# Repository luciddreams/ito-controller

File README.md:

# ITO Controller — Condensation Mirror

KiCad 9 project for a 100 × 100 mm ITO glass plate with resistive heating and four independently regulated TEC1-12706 cooling channels. Controller: Seeed XIAO BLE nRF52840. Supply: Mean Well GST160A24-R7B, connected directly to J30 (Kycon KPJX-4S).

**Status:** revision L, supervised prototype; no assembled hardware has been tested. Maximum actual total input current: 4 A. Firmware L.1 supports short manual tests with one TEC at a time. Automatic condensation/dew-point control is not implemented.

## Start here

- [Detailed project description](docs/PROJECT-DESCRIPTION.md): circuit operation, thermal concept, operating limits and outstanding work.
- [Schematic PDF](ito-controller-schema-rev-l.pdf) and [schematic reading guide](SCHEMATIC-GUIDE.md).
- Open `ito-controller.kicad_pro` in KiCad 9 for the schematic, PCB and 3D viewer. Keep the directory structure intact.
- [Datasheets and BOM coverage](datasheets/README.md).
- [Purchasing BOM and order tracker](procurement/README.md): ordered/delivered checkboxes, suppliers, prices and quantities.
- [Assembly and wiring](ASSEMBLY.md), [connector pinout](connector-pinout.csv) and [prototype commissioning](PROTOTYPE-START.md).
- [Firmware build, flashing and calibration](firmware/README.md) and [GPIO/I²C contract](FIRMWARE-INTERFACE.md).

## Repository contents

| Path | Contents |
|---|---|
| `ito-controller.kicad_*`, `sheet_*.kicad_sch` | Editable PCB and 14-page schematic |
| `ITO.kicad_sym`, `ITO_PCB.pretty/`, `3dmodels/` | Local symbols, footprints and models |
| `manufacturing/` | Gerbers, drills, placement files and fabrication output |
| `BOM-prototype.csv` | Component references, manufacturers and orderable part numbers |
| `external-sensor-BOM.csv` | External ambient modules and cable parts |
| `procurement/` | Browser purchasing tracker, Excel alternative and instructions |
| `firmware/` | Source code, diagnostic build and host tests |
| `datasheets/` | Manufacturer documents, source URLs and download status |
| `docs/` | Detailed description and import information |
| `*-review.json`, `*-parity.json`, `*.rpt` | Design checks and comparison reports |
| `commissioning-results.csv` | Physical tests awaiting execution |
| `history-rev-j/`, `history-rev-k/` | Historical records; not current construction instructions |

## Fabrication and verification

Read [FABRICATION.md](FABRICATION.md) before ordering: four layers, 160 × 110 mm, 1.6 mm thick, 70/35/35/70 µm copper, with specified via-in-pad processing. Assemble one prototype first.

Existing reports record zero ERC/DRC violations and schematic/PCB parity for 202 components and 638 pins. The readable-schematic revision preserved the PCB. Design checks and firmware host tests do not replace physical commissioning.

## Next engineering steps

1. Select the exact NTC probes, fan, cooling assembly and glass coating.
2. Inspect the unloaded board and verify auxiliary supplies.
3. Measure with dummy loads and enter firmware calibration data.
4. Qualify one TEC, then the glass, using short limited-power pulses.
5. Develop four-channel operation and automatic dew-point control only after qualification.

Remote SHT31 sensors require the complete adapter and jumper instructions in [REMOTE-SENSORS.md](REMOTE-SENSORS.md). Their RJ45 links are not Ethernet or PoE.

## Language and licensing

English is the working language for current documentation and schematic annotations. Original historical engineering records are retained in their original language for traceability; see [historical records](docs/HISTORICAL-RECORDS.md). Manufacturer PDFs retain the language supplied by their authors. Legacy component Value fields and net identifiers remain stable for CAD/BOM compatibility.

No open-source license has been selected for the project's own hardware or firmware. Third-party documents and models retain their original rights and licenses; see [THIRD-PARTY-NOTICES.md](THIRD-PARTY-NOTICES.md).

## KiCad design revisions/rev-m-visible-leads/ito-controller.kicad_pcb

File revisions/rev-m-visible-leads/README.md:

# Revision M — visible-lead prototype

This independent KiCad project replaces the five QFN ICs in revision L. Signal pins on U1 and U11–U14 are exposed gull-wing leads. Their grounded thermal pads still require soldering. The original manufactured design at the repository root is unchanged.

**Engineering prototype, not a bench-qualified production release.** See `review/STATUS.md` for the actual checks and outstanding release gates. Do not use revision-L Gerbers, stencil, component placement or calibration for this board.

## Main changes

| Circuit | Revision L | Revision M |
|---|---|---|
| U1 input eFuse | TPS26630RGER, QFN24 | TPS26631PWPR, HTSSOP20 + ground pad |
| U11–U14 TEC control | LT8613EUDE, QFN28 | LT3741EFE-1#PBF, TSSOP20 + ground pad |
| TEC switches | Inside LT8613 | Two IRLR024NTRPBF DPAK MOSFETs per channel |
| L1–L4 | 10 µH IHLP6767 | 33 µH Bourns SRP1265A-330M |
| Switching frequency | Nominal 500 kHz | Nominal 300 kHz |
| TP11–TP14 monitoring | LT8613 IMON | INA180A1IDBVR, SOT23-5, 0.5 V/A nominal |
| Board | 160 × 110 mm, four layers | 160 × 128 mm, four layers |

The upper mounting holes and four TEC connector locations are retained. Lower circuitry, lower mounting holes and the antenna keepout move down 18 mm. This revision therefore requires a mechanical fit check. The lower schematic functions, GPIO assignments, I²C addresses, relay/thermostat chain and heater interlock remain unchanged.

Open **`ito-controller.kicad_pro` in this directory** with KiCad 9. The symbol and footprint libraries are local. Existing 3D models are referenced from `../../3dmodels`; new package footprints currently have no 3D models. Electrical and fabrication geometry does not depend on those models.

## Electrical differences that matter

- TPS26631 is **not fault-identical** to TPS26630. After PGOOD, it permits approximately twice the programmed current for nominally 25.5 ms. With 4.02 kΩ, nominal sustained limit is approximately 4.48 A and the temporary limit approximately 8.96 A. Actual operating input current must still remain at or below 4 A. Verify the adapter, fuse, reset and interlock response with the new eFuse.
- LT3741-1 controls **average inductor current** and does not intentionally sink current. The 25 mΩ shunt is now before the output capacitors. TP monitoring therefore includes inductor ripple and capacitor charging current. Use an external meter/current probe in the TEC lead for load-current calibration.
- R42/R44/R46/R48 change to 4.02 kΩ. The lower 10 kΩ resistors and buffers remain. Full DAC code gives approximately 1.460 V at CTRL1. Expected nominal full-scale current is about 1.99 A using the 51 mV reference specification; part tolerances can produce over 2 A. This is **not a guaranteed 2 A limiter**. Calibrate each channel and use conservative code limits.
- The nominal voltage ceiling is 11.94 V. The 22.1 kΩ / 6.8 nF compensation network is a calculated starting point. C109/C209/C309/C409 are optional 100 pF compensation footprints and **DNP** initially.
- IRLR024N has a maximum 2 V threshold at 25 °C, at the boundary of ADI's recommendation of less than 2 V. Startup/recovery and cold operation are explicit qualification gates. The footprint permits reviewing another pin-compatible DPAK part if this gate fails; substitution is not automatic.

The diagnostic firmware at `../../firmware` writes raw DAC codes and retains the same GPIO/I²C interface. Use its default disabled calibration state. **Do not carry over measured TEC code limits from revision L.** This revision does not turn that firmware into an automatic or unattended controller.

## Files

- Native schematics, PCB and local libraries: editable design.
- `design.json`: component pin/net and ordering data.
- `BOM-prototype.csv`: individual references; Fit column identifies the four DNP options.
- `review/`: calculation results, clean ERC/DRC/parity reports and prototype test gates.
- `fabrication/`: prototype Gerber/drill archive and manufacturing notes.
- `tools/`: reproducible design transformation, calculation and audit helpers. Generation starts from the unchanged revision-L project; final routed PCB is the authoritative layout.

Changing a package or component value can affect compensation, protection or assembly. Read `review/DESIGN-REVIEW.md` before ordering alternatives.

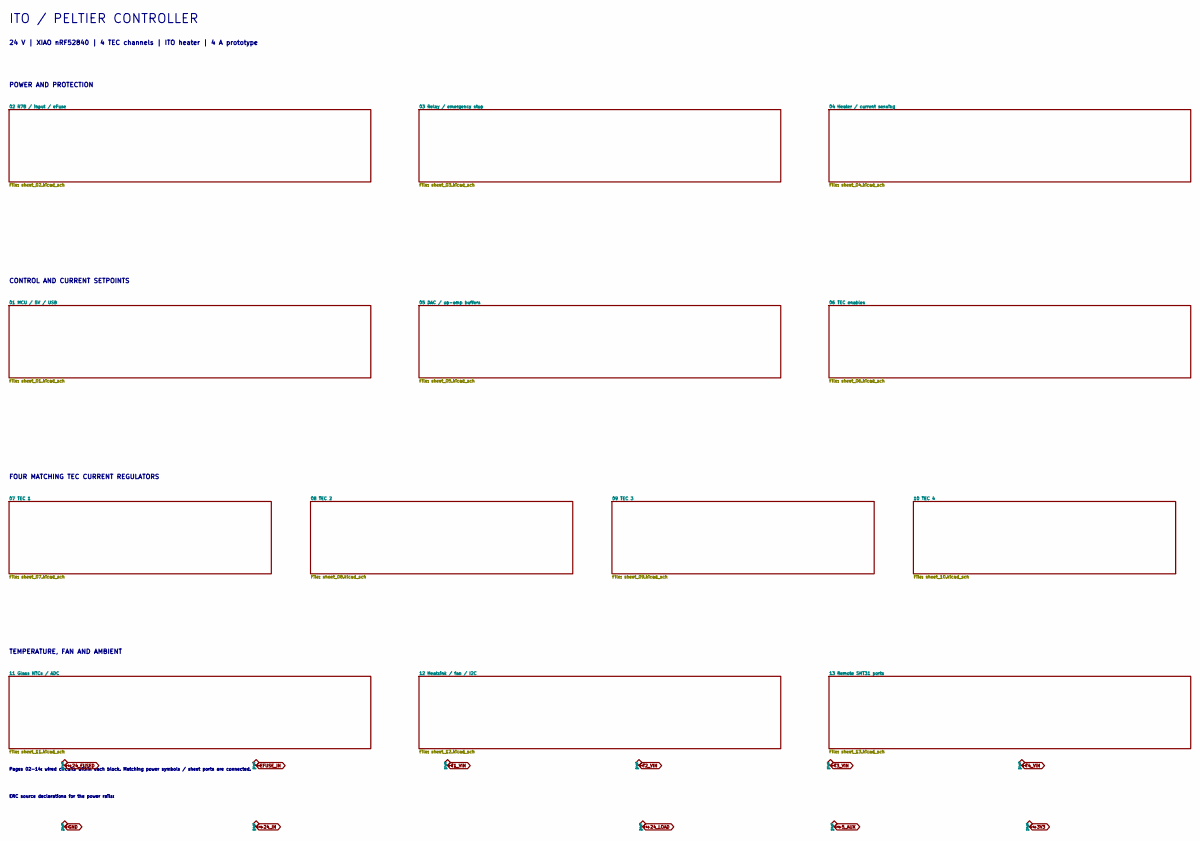
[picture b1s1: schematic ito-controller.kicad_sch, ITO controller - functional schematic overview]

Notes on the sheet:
ITO / PELTIER CONTROLLER
24 V | XIAO nRF52840 | 4 TEC channels | ITO heater | 4 A prototype
POWER AND PROTECTION
CONTROL AND CURRENT SETPOINTS
FOUR MATCHING TEC CURRENT REGULATORS
TEMPERATURE, FAN AND AMBIENT
ERC source declarations for the power rails:
Pages 02-14: wired circuits within each block. Matching power symbols / sheet ports are connected.

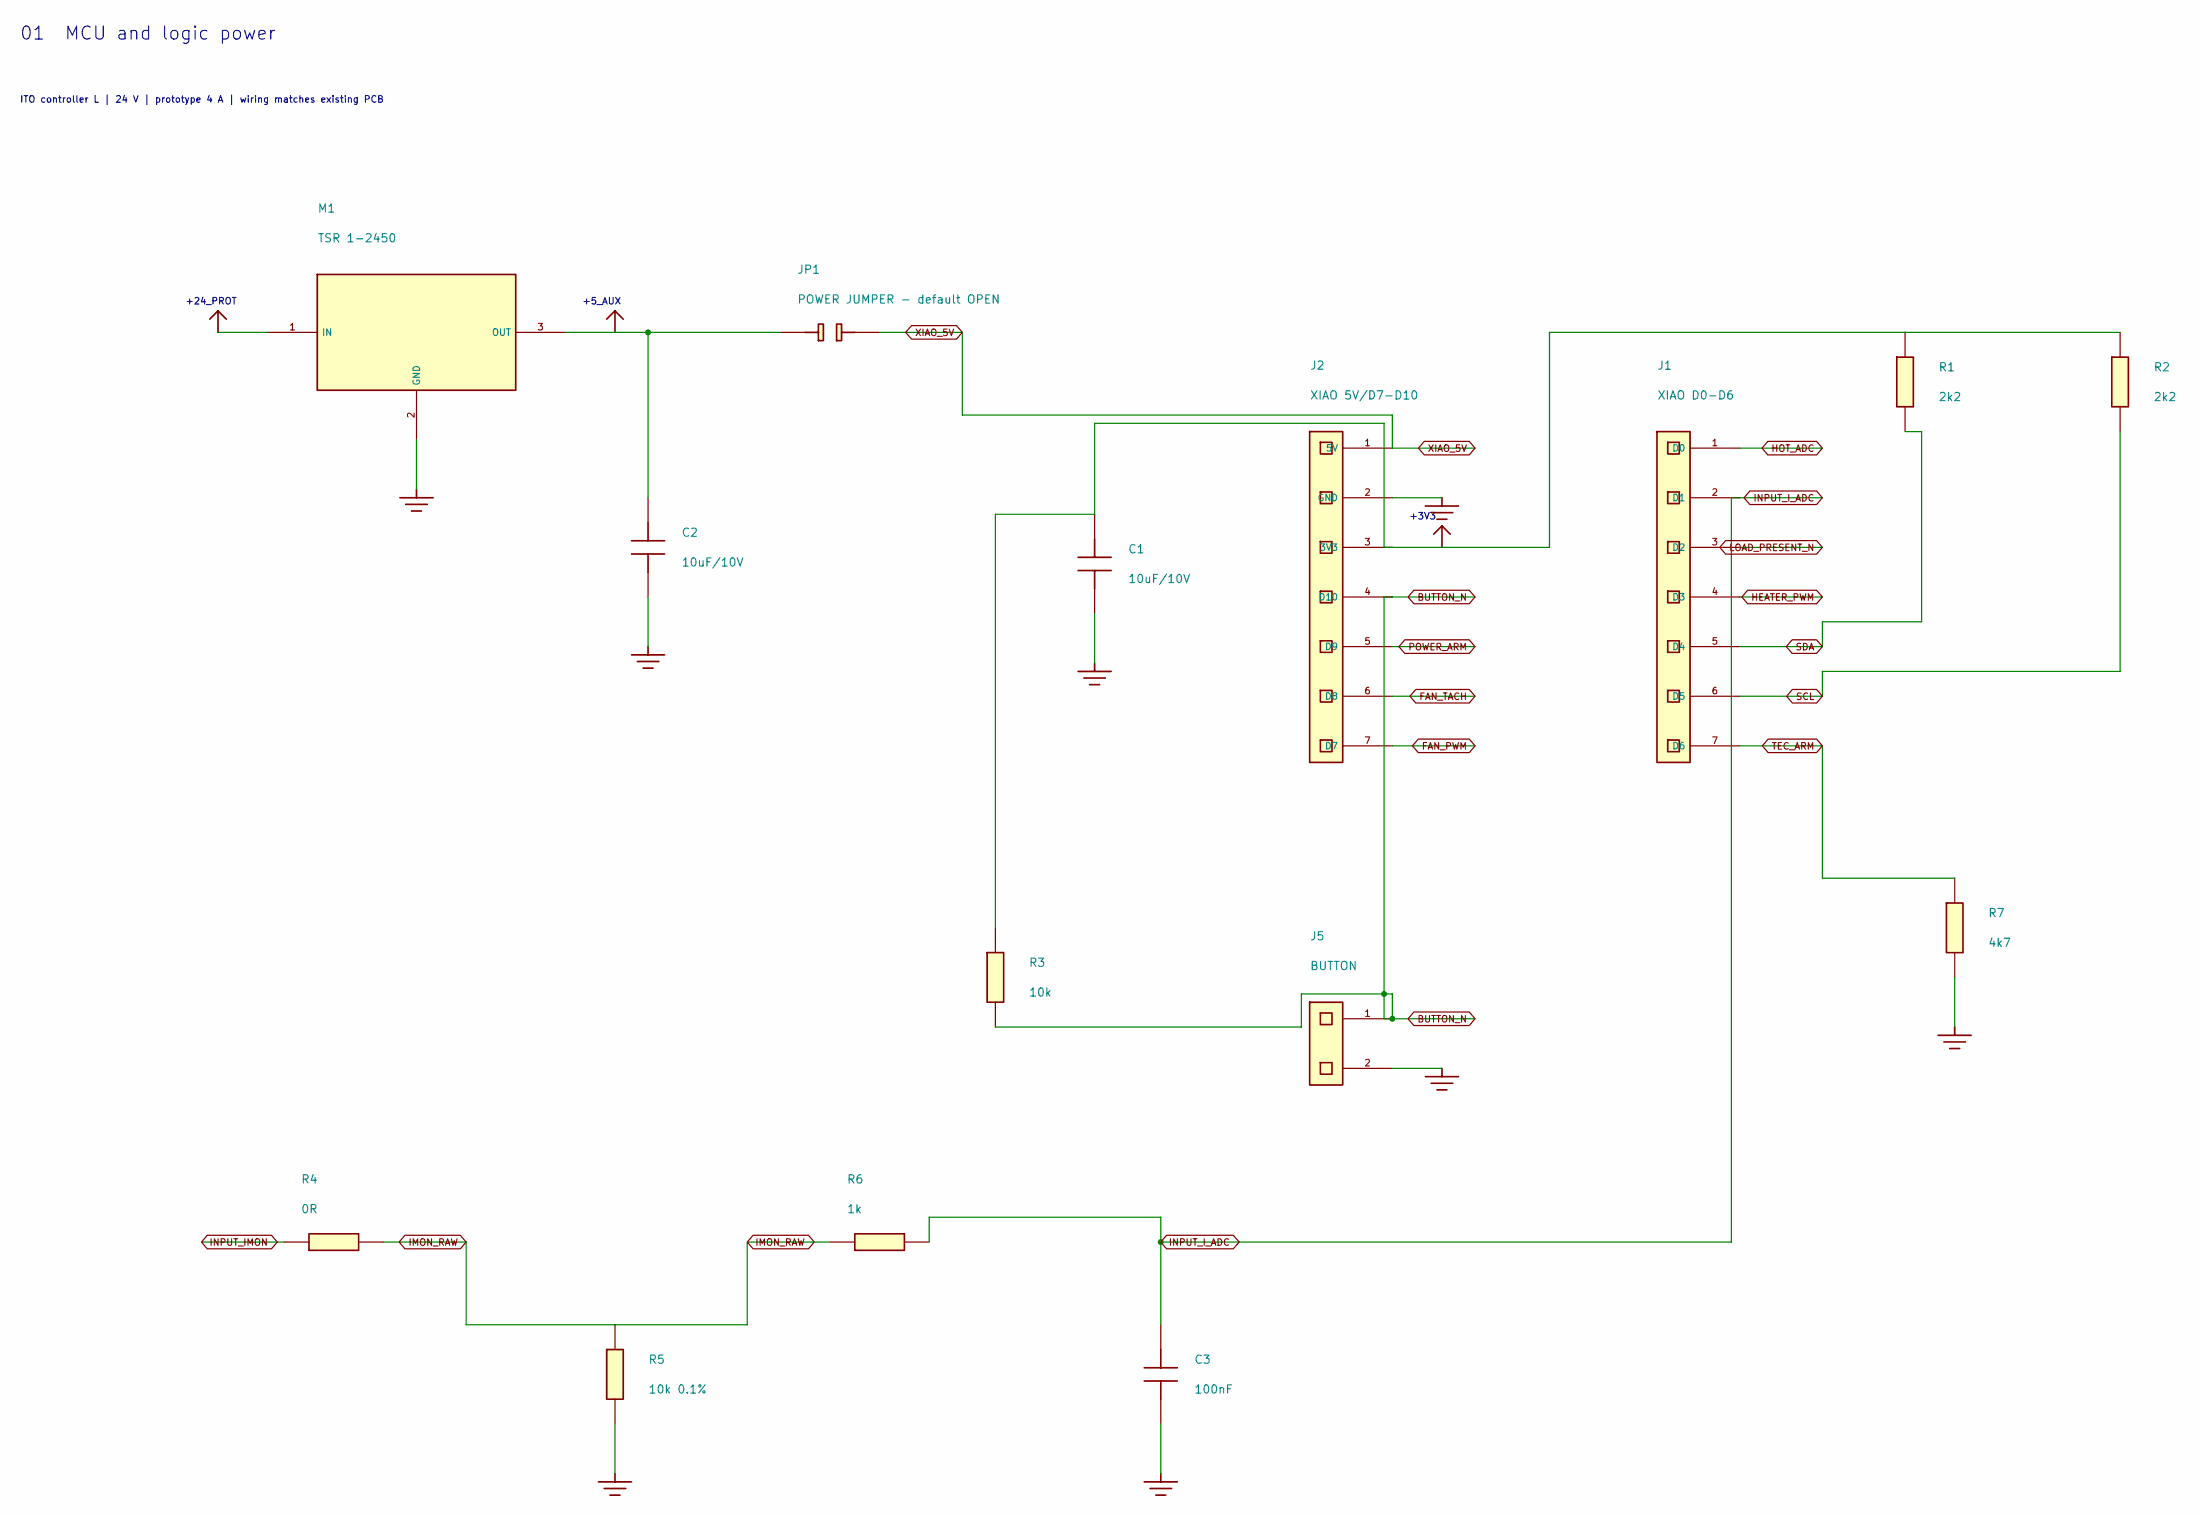
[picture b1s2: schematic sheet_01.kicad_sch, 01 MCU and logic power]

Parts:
C1, C2: 10u / 10V; C_0805_2012Metric; MPN GRM21BR61E106KA73L
C3: 100n; C_0805_2012Metric; MPN GRM21BR71H104KA01L
J1: XIAO right socket 1x7 - USB down; PinSocket_1x07_P2.54mm_Vertical; MPN SSW-107-01-G-S
J2: XIAO left socket 1x7 - USB down; PinSocket_1x07_P2.54mm_Vertical; MPN SSW-107-01-G-S
J5: Connector 2 pins; JST_XH_B2B-XH-A_1x02_P2.50mm_Vertical; MPN B2B-XH-A(LF)(SN)
JP1: Voedingsjumper - standaard OPEN; PinHeader_1x02_P2.54mm_Vertical; MPN TSW-102-07-G-S
M1: TSR 1-2450; Converter_DCDC_TRACO_TSR-1_THT; MPN TSR 1-2450
R1, R2: 2k2; R_0805_2012Metric; MPN RC0805FR-072K2L
R3: 10k; R_0805_2012Metric; MPN RC0805FR-0710KL
R4: 0R; R_0805_2012Metric; MPN RC0805JR-070RL
R5: 10k 0.1%; R_0805_2012Metric; MPN RT0805BRD0710KL
R6: 1k; R_0805_2012Metric; MPN RC0805FR-071KL
R7: 4k7; R_0805_2012Metric; MPN RC0805FR-074K7L

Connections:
+3V3: C1.1, J2.3 (3V3), R1.1, R2.1, R3.1; also elsewhere on the board
+5_AUX: C2.1, JP1.1, M1.3 (OUT); also elsewhere on the board
+24_PROT: M1.1 (IN); also elsewhere on the board
BUTTON_N: J2.4 (D10), J5.1, R3.2
FAN_PWM: J2.7 (D7); also elsewhere on the board
FAN_TACH: J2.6 (D8); also elsewhere on the board
GND: C1.2, C2.2, C3.2, J2.2 (GND), J5.2, M1.2 (GND), R5.2, R7.2; also elsewhere on the board
HEATER_PWM: J1.4 (D3); also elsewhere on the board
HOT_ADC: J1.1 (D0); also elsewhere on the board
IMON_RAW: R4.2, R5.1, R6.1
INPUT_IMON: R4.1; also elsewhere on the board
INPUT_I_ADC: C3.1, J1.2 (D1), R6.2
LOAD_PRESENT_N: J1.3 (D2); also elsewhere on the board
POWER_ARM: J2.5 (D9); also elsewhere on the board
SCL: J1.6 (D5), R2.2; also elsewhere on the board
SDA: J1.5 (D4), R1.2; also elsewhere on the board
TEC_ARM: J1.7 (D6), R7.1; also elsewhere on the board
XIAO_5V: J2.1 (5V), JP1.2

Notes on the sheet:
+3V3
+24_PROT
+5_AUX
01 MCU and logic power
ITO controller L | 24 V | prototype 4 A | wiring matches existing PCB

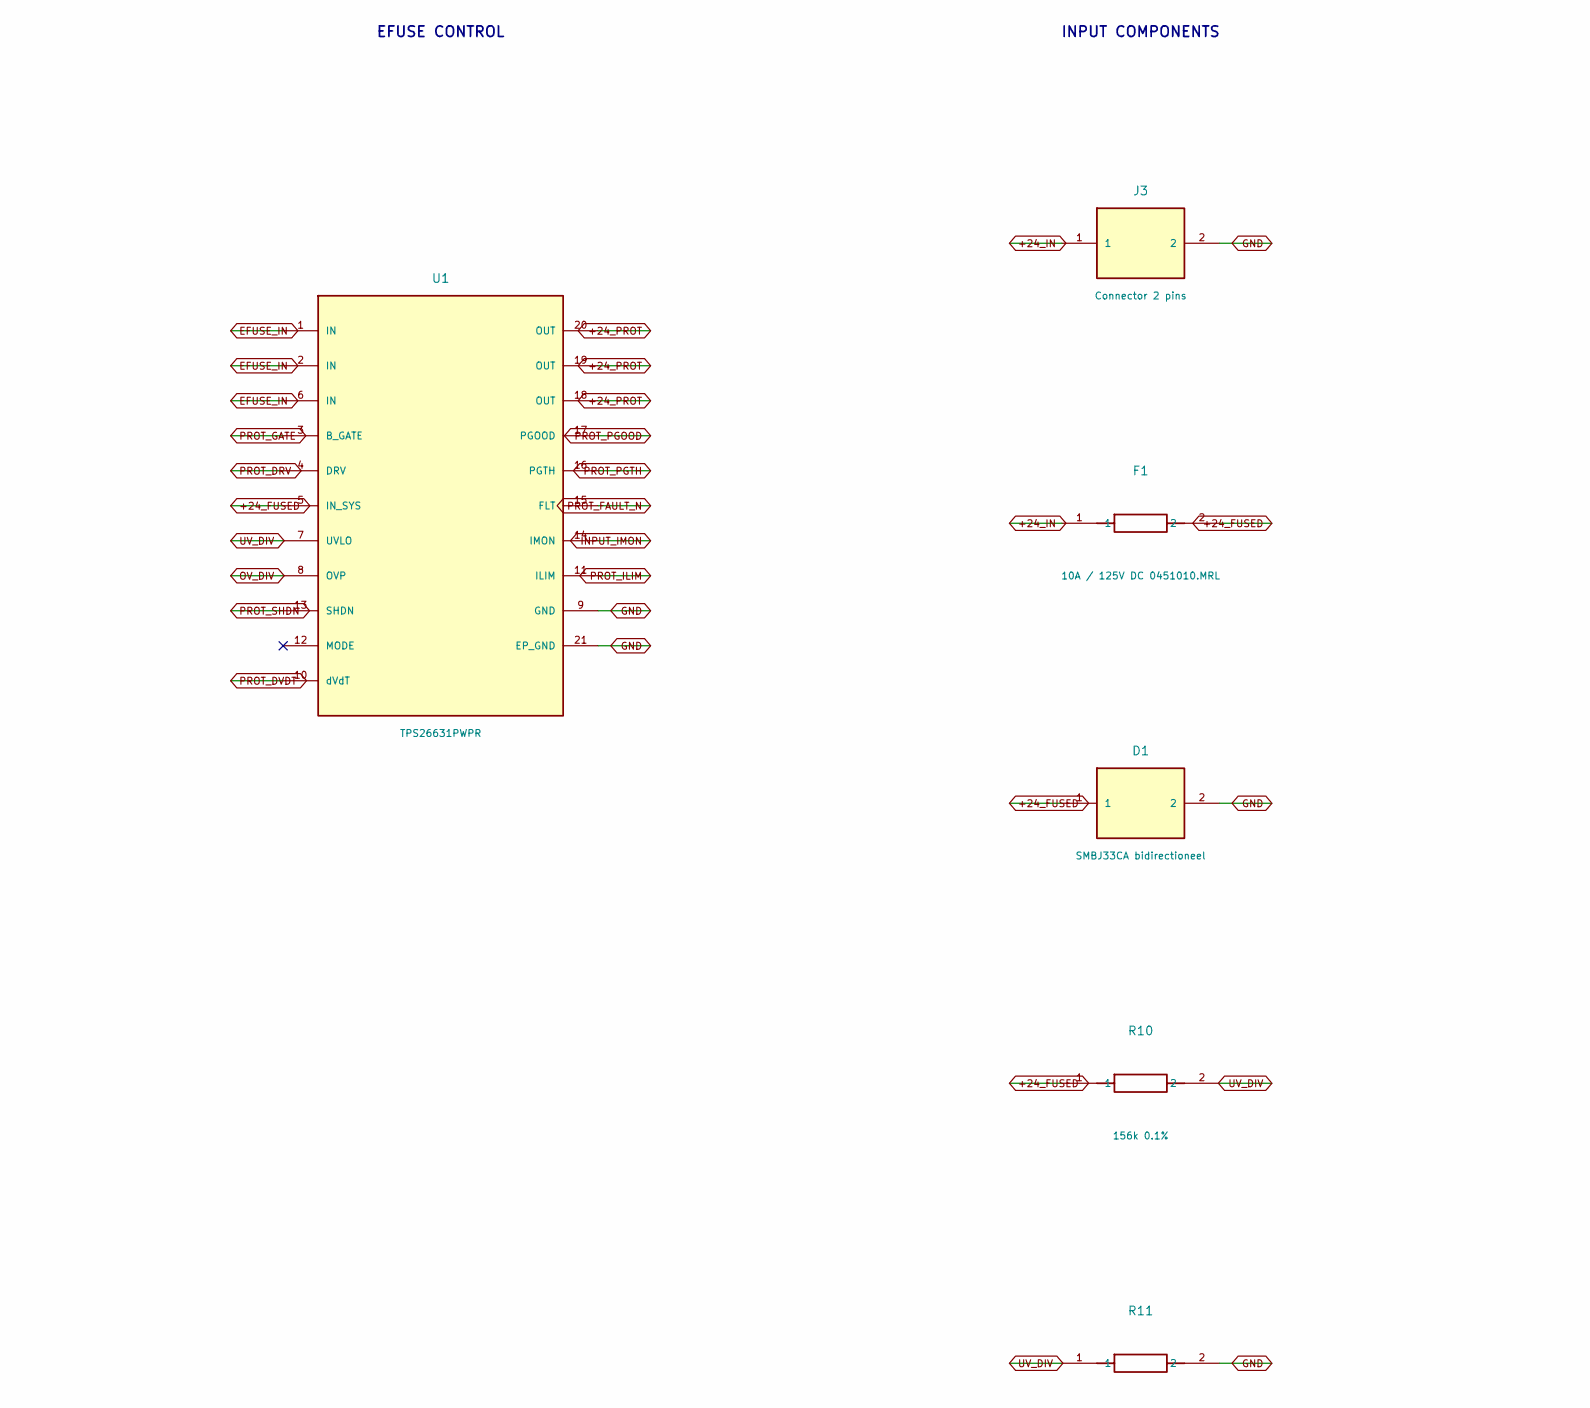
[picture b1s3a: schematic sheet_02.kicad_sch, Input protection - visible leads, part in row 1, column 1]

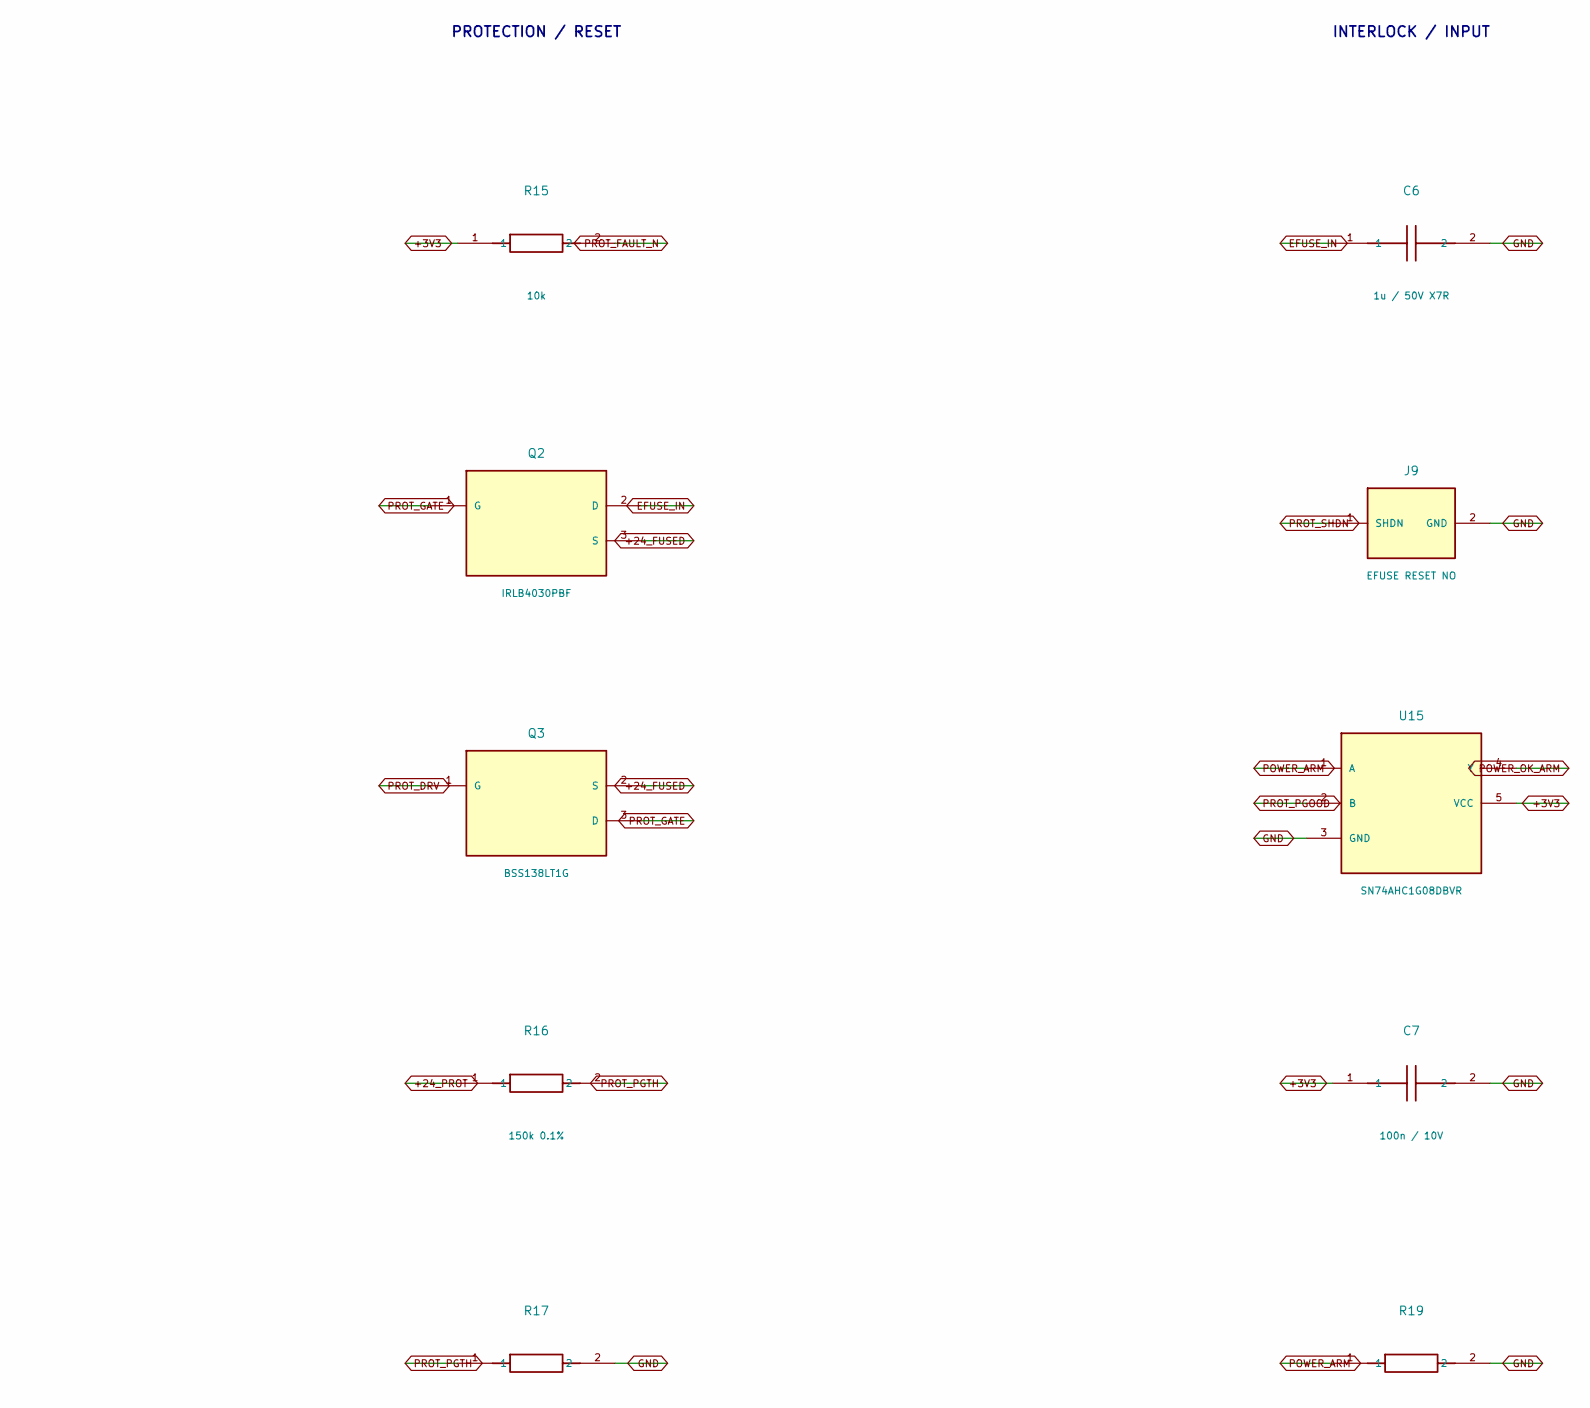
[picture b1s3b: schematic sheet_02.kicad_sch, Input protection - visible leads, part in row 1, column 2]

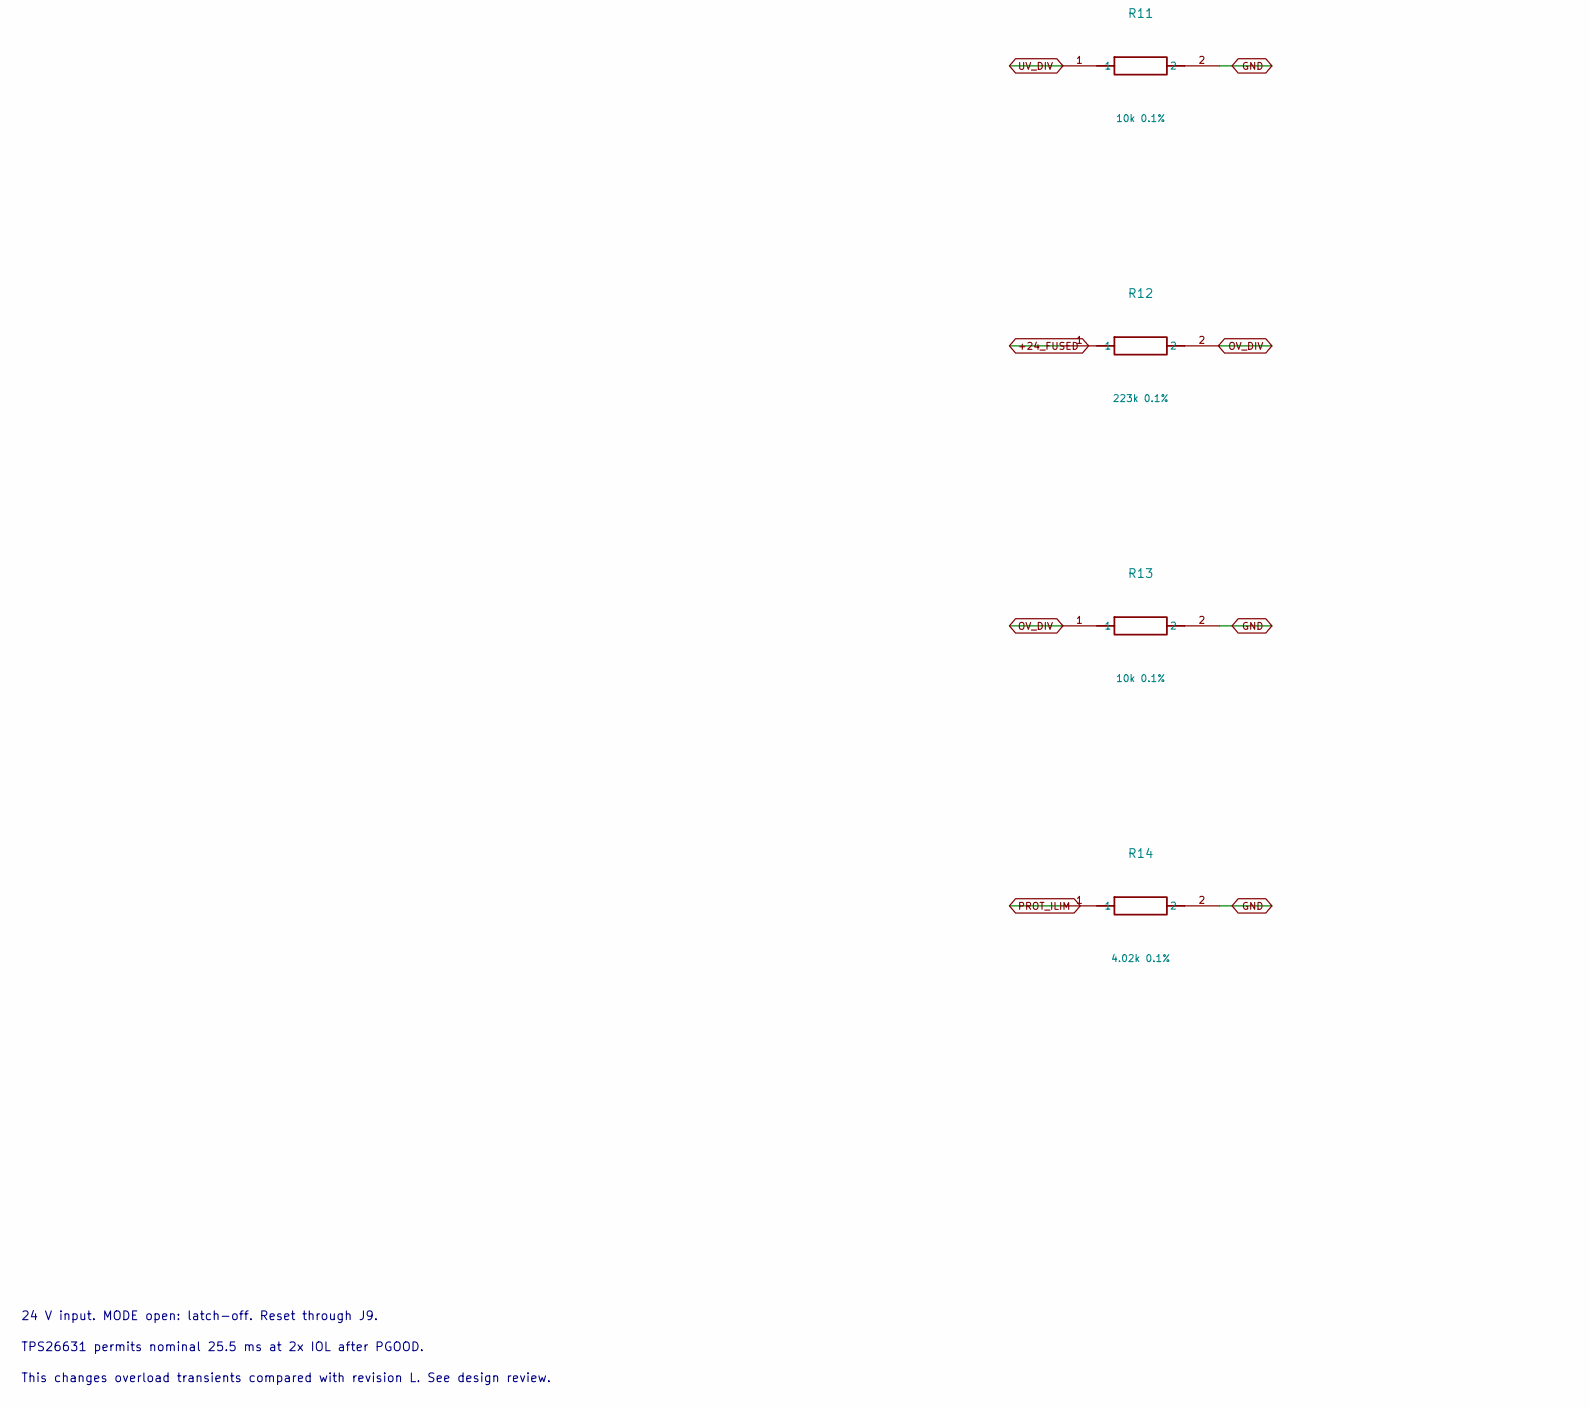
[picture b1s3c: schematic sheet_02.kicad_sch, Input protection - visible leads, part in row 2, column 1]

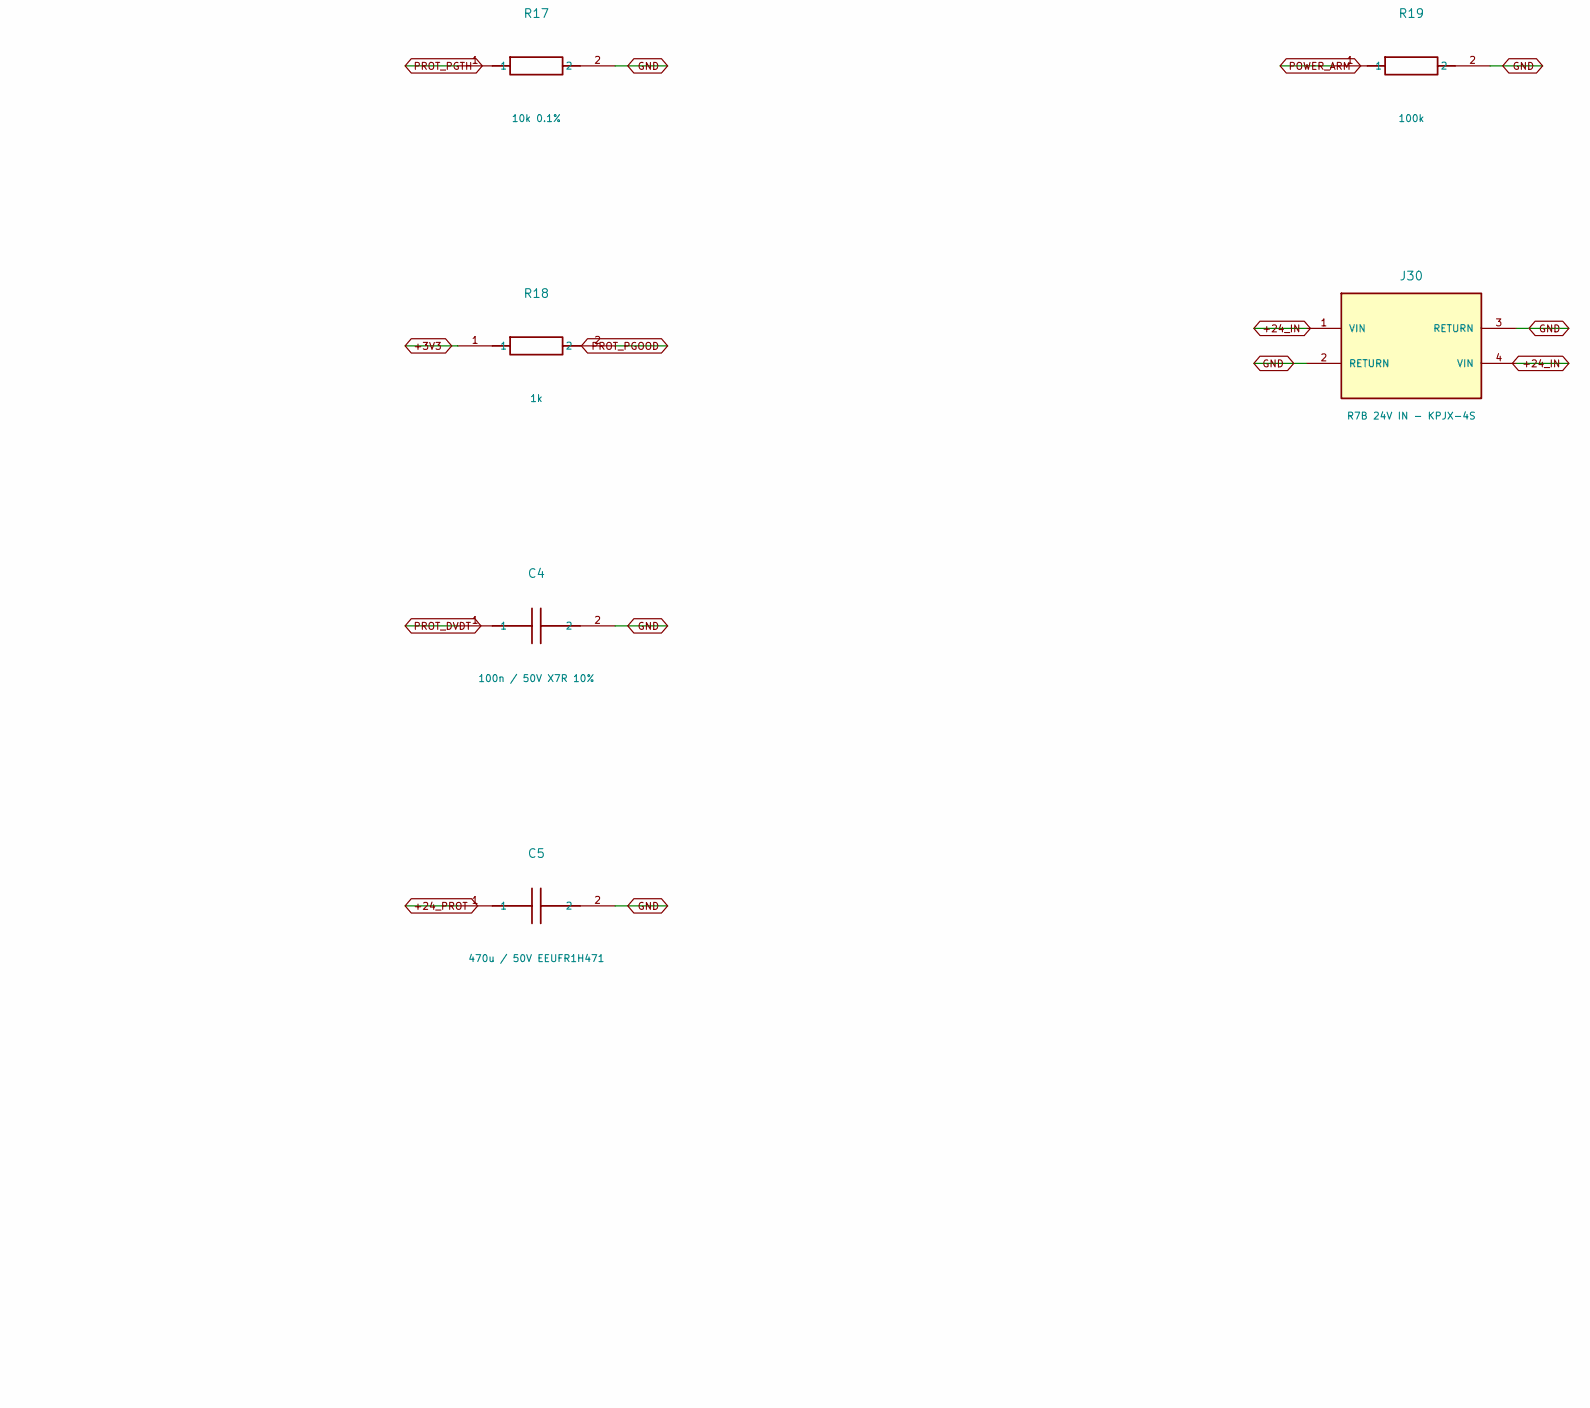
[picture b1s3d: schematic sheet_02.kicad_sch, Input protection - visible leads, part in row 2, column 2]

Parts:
C4: 100n / 50V X7R 10%; C_0805_2012Metric; MPN GRM21BR71H104KA01L
C5: 470u / 50V EEUFR1H471; CP_Radial_D12.5mm_P5.00mm; MPN EEUFR1H471
C6: 1u / 50V X7R; C_0805_2012Metric; MPN GRM21BR71H105KA12L
C7: 100n / 10V; C_0805_2012Metric; MPN GRM21BR71H104KA01L
D1: SMBJ33CA bidirectioneel; D_SMB; MPN SMBJ33CA
F1: 10A / 125V DC 0451010.MRL; Littelfuse_451; MPN 0451010.MRL
J3: Connector 2 pins; TerminalBlock_Phoenix_MKDS-1,5-2-5.08_1x02_P5.08mm_Horizont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; MPN 1715721
J9: EFUSE RESET NO; JST_XH_B2B-XH-A_1x02_P2.50mm_Vertical; MPN B2B-XH-A(LF)(SN)
J30: R7B 24V IN - KPJX-4S; Kycon_KPJX-4S; MPN KPJX-4S
Q2: IRLB4030PBF; TO-220-3_Vertical; MPN IRLB4030PBF
Q3: BSS138LT1G; SOT-23; MPN BSS138LT1G
R10: 156k 0.1%; R_0805_2012Metric; MPN RT0805BRD07156KL
R11, R13, R17: 10k 0.1%; R_0805_2012Metric; MPN RT0805BRD0710KL
R12: 223k 0.1%; R_0805_2012Metric; MPN RT0805BRD07223KL
R14: 4.02k 0.1%; R_0805_2012Metric; MPN RT0805BRD074K02L
R15: 10k; R_0805_2012Metric; MPN RC0805FR-0710KL
R16: 150k 0.1%; R_0805_2012Metric; MPN RT0805BRD07150KL
R18: 1k; R_0805_2012Metric; MPN RC0805FR-071KL
R19: 100k; R_0805_2012Metric; MPN RC0805FR-07100KL
U1: TPS26631PWPR; TI_PWP0020T_EP2.96; MPN TPS26631PWPR
U15: SN74AHC1G08DBVR; SOT-23-5; MPN SN74AHC1G08DBVR

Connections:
+3V3: C7.1, R15.1, R18.1, U15.5 (VCC); also elsewhere on the board
+24_FUSED: D1.1, F1.2, Q2.3 (S), Q3.2 (S), R10.1, R12.1, U1.5 (IN_SYS)
+24_IN: F1.1, J3.1, J30.1 (VIN), J30.4 (VIN)
+24_PROT: C5.1, R16.1, U1.18 (OUT), U1.19 (OUT), U1.20 (OUT); also elsewhere on the board
EFUSE_IN: C6.1, Q2.2 (D), U1.1 (IN), U1.2 (IN), U1.6 (IN)
GND: C4.2, C5.2, C6.2, C7.2, D1.2, J3.2, J9.2 (GND), J30.2 (RETURN), J30.3 (RETURN), R11.2, R13.2, R14.2, R17.2, R19.2, U1.9 (GND), U1.21 (EP_GND), U15.3 (GND); also elsewhere on the board
INPUT_IMON: U1.14 (IMON); also elsewhere on the board
OV_DIV: R12.2, R13.1, U1.8 (OVP)
POWER_ARM: R19.1, U15.1 (A); also elsewhere on the board
POWER_OK_ARM: U15.4 (Y); also elsewhere on the board
PROT_DRV: Q3.1 (G), U1.4 (DRV)
PROT_DVDT: C4.1, U1.10 (dVdT)
PROT_FAULT_N: R15.2, U1.15 (FLT); also elsewhere on the board
PROT_GATE: Q2.1 (G), Q3.3 (D), U1.3 (B_GATE)
PROT_ILIM: R14.1, U1.11 (ILIM)
PROT_PGOOD: R18.2, U1.17 (PGOOD), U15.2 (B)
PROT_PGTH: R16.2, R17.1, U1.16 (PGTH)
PROT_SHDN: J9.1 (SHDN), U1.13 (SHDN)
UV_DIV: R10.2, R11.1, U1.7 (UVLO)

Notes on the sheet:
EFUSE CONTROL
INPUT COMPONENTS
PROTECTION / RESET
INTERLOCK / INPUT
24 V input. MODE open: latch-off. Reset through J9.
TPS26631 permits nominal 25.5 ms at 2x IOL after PGOOD.
This changes overload transients compared with revision L. See design review.
